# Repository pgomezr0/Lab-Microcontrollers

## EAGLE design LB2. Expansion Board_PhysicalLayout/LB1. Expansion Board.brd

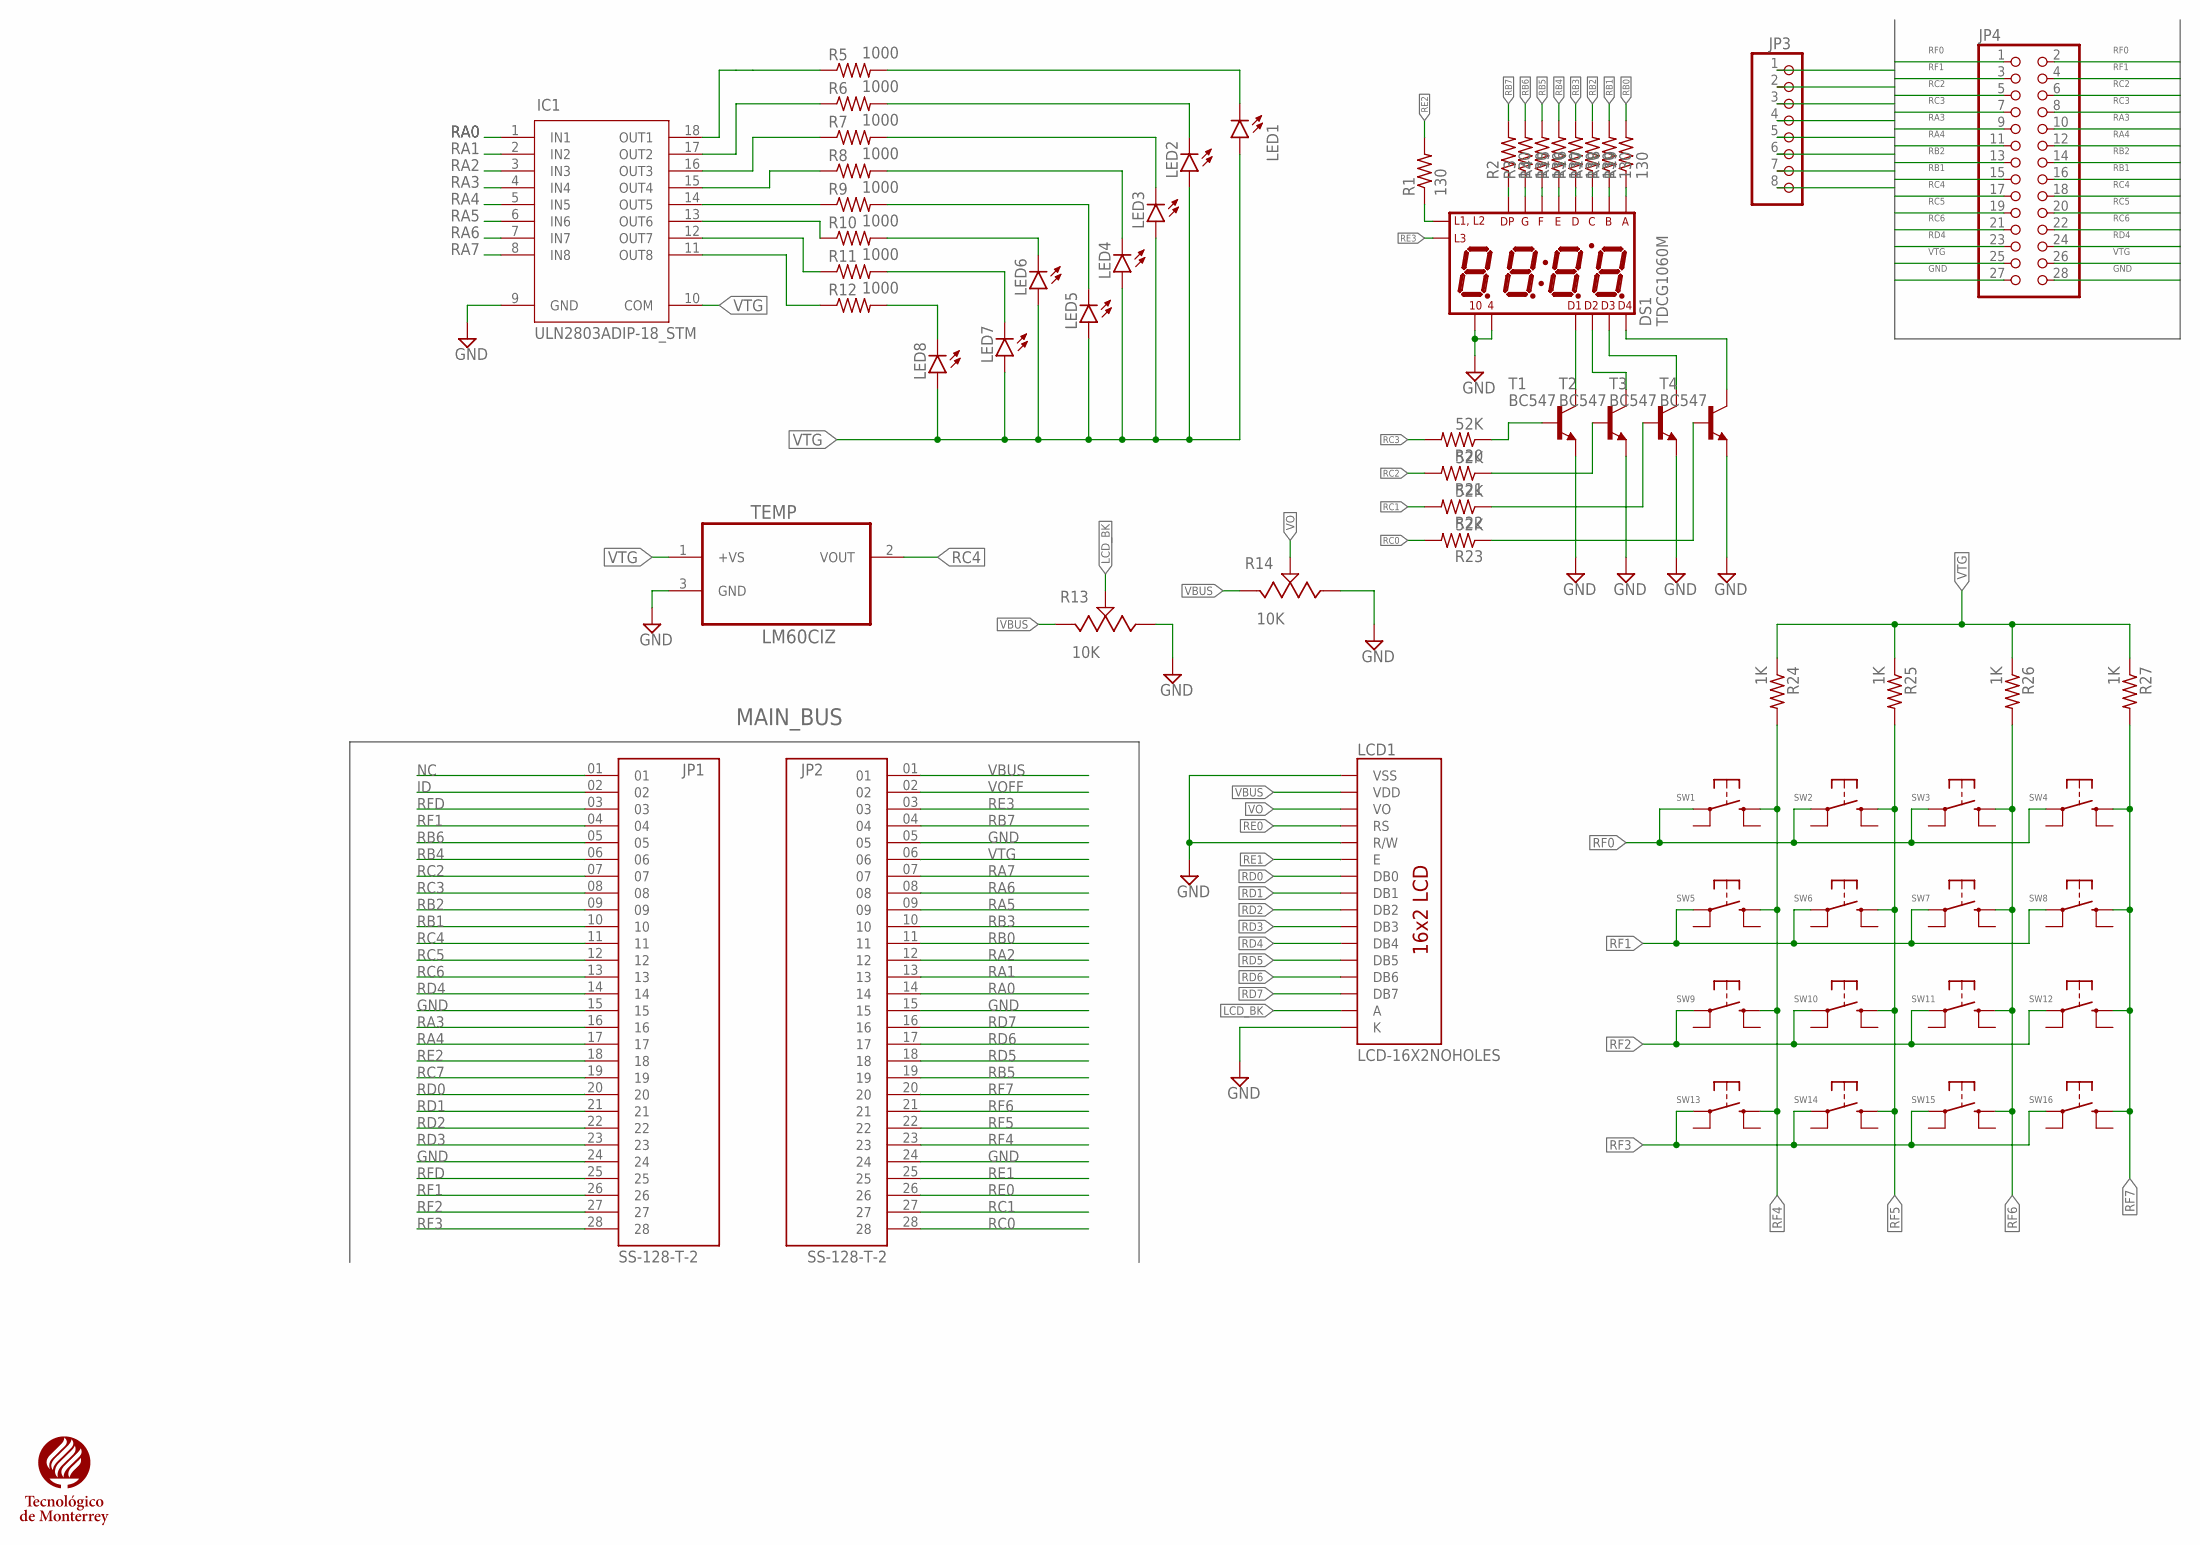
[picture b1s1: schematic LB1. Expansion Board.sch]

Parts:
DS1: TDCG1060M; DISPLAY_TDCG1060M
IC1: ULN2803ADIP-18_STM; DIP-18_STM
JP1, JP2: SS-128-T-2; SAMTEC_SS-128-T-2
JP3: PINHD-1X8BIG; 1X08-BIG
JP4: PINHD-2X14-CB; 2X14-BIG
LCD1: LCD-16X2NOHOLES; LCD-16X2_NOHOLESNOSILK
LED1, LED2, LED3, LED4, LED5, LED6, LED7, LED8: LED3MM
R1, R2, R3, R4, R15, R16, R17, R18, R19: 130; 0207/10
R5, R6, R7, R8, R9, R10, R11, R12: 1000; 0207/10
R13, R14: 10K; 3362P-1-103LF
R20, R21, R22, R23: 52K; 0207/10
R24, R25, R26, R27: 1K; 0207/10
SW1, SW2, SW3, SW4, SW5, SW6, SW7, SW8, SW9, SW10, SW11, SW12, SW13, SW14, SW15, SW16: 1825910-2; TE_1825910-2
T1, T2, T3, T4: BC547; TO92
TEC1: TEC_LOGO
TEMP: LM60CIZ; TO92/

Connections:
GND: DS1.4, DS1.10, IC1.9 (GND), JP1.15, JP1.24, JP2.05, JP2.15, JP2.24, JP3.1, JP4.27, JP4.28, LCD1.1 (VSS), LCD1.5 (R/W), LCD1.16 (K), R13.3, R14.3, T1.1 (E), T2.1 (E), T3.1 (E), T4.1 (E), TEMP.3 (GND)
ID: JP1.02
LCD_BK: LCD1.15 (A), R13.2
unnamed: LED1.K (C), R5.2
unnamed: IC1.18 (OUT1), R5.1
unnamed: IC1.17 (OUT2), R6.1
unnamed: LED2.K (C), R6.2
unnamed: IC1.16 (OUT3), R7.1
unnamed: IC1.15 (OUT4), R8.1
unnamed: IC1.14 (OUT5), R9.1
unnamed: IC1.13 (OUT6), R10.1
unnamed: IC1.12 (OUT7), R11.1
unnamed: IC1.11 (OUT8), R12.1
unnamed: LED3.K (C), R7.2
unnamed: LED4.K (C), R8.2
unnamed: LED5.K (C), R9.2
unnamed: LED6.K (C), R10.2
unnamed: LED8.K (C), R12.2
unnamed: LED7.K (C), R11.2
unnamed: R20.1, T1.2 (B)
unnamed: LED1.A, LED2.A, LED3.A, LED4.A, LED5.A, LED6.A, LED7.A, LED8.A
unnamed: DS1.12 (L1_L2), R1.1
unnamed: DS1.7 (DP), R2.1
unnamed: DS1.15 (G), R3.1
unnamed: DS1.11 (F), R4.1
unnamed: DS1.5 (E), R15.1
unnamed: DS1.3 (D), R16.1
unnamed: DS1.13 (C), R17.1
unnamed: DS1.16 (B), R18.1
unnamed: DS1.14 (A), R19.1
unnamed: R21.1, T2.2 (B)
unnamed: R22.1, T3.2 (B)
unnamed: R23.1, T4.2 (B)
unnamed: DS1.1 (DIG1), T1.3 (C)
unnamed: DS1.2 (DIG2), T2.3 (C)
unnamed: DS1.6 (DIG3), T3.3 (C)
unnamed: DS1.8 (DIG4), T4.3 (C)
NC: JP1.01
RA0: IC1.1 (IN1), JP2.14
RA1: IC1.2 (IN2), JP2.13
RA2: IC1.3 (IN3), JP2.12
RA3: IC1.4 (IN4), JP1.16, JP3.2, JP4.9, JP4.10
RA4: IC1.5 (IN5), JP1.17, JP3.3, JP4.11, JP4.12
RA5: IC1.6 (IN6), JP2.09
RA6: IC1.7 (IN7), JP2.08
RA7: IC1.8 (IN8), JP2.07
RB0: JP2.11, R19.2
RB1: JP1.10, JP3.4, JP4.15, JP4.16, R18.2
RB2: JP1.09, JP3.5, JP4.13, JP4.14, R17.2
RB3: JP2.10, R16.2
RB4: JP1.06, R15.2
RB5: JP2.19, R4.2
RB6: JP1.05, R3.2
RB7: JP2.04, R2.2
RC0: JP2.28, R23.2
RC1: JP2.27, R22.2
RC2: JP1.07, JP3.6, JP4.5, JP4.6, R21.2
RC3: JP1.08, JP3.7, JP4.7, JP4.8, R20.2
RC4: JP1.11, JP3.8, JP4.17, JP4.18, TEMP.2 (VOUT)
RC5: JP1.12, JP4.19, JP4.20
RC6: JP1.13, JP4.21, JP4.22
RC7: JP1.19
RD0: JP1.20, LCD1.7 (DB0)
RD1: JP1.21, LCD1.8 (DB1)
RD2: JP1.22, LCD1.9 (DB2)
RD3: JP1.23, LCD1.10 (DB3)
RD4: JP1.14, JP4.23, JP4.24, LCD1.11 (DB4)
RD5: JP2.18, LCD1.12 (DB5)
RD6: JP2.17, LCD1.13 (DB6)
RD7: JP2.16, LCD1.14 (DB7)
RE0: JP2.26, LCD1.4 (RS)
RE1: JP2.25, LCD1.6 (E)
RE2: JP1.18, R1.2
RE3: DS1.9 (L3), JP2.03
RF0: JP4.1, JP4.2, SW1.1, SW2.1, SW3.1, SW4.1
RF1: JP1.04, JP1.26, JP4.3, JP4.4, SW5.1, SW6.1, SW7.1, SW8.1
RF2: JP1.27, SW9.1, SW10.1, SW11.1, SW12.1
RF3: JP1.28, SW13.1, SW14.1, SW15.1, SW16.1
RF4: JP2.23, R24.2, SW1.2 (S), SW5.2 (S), SW9.2 (S), SW13.2 (S)
RF5: JP2.22, R25.2, SW2.2 (S), SW6.2 (S), SW10.2 (S), SW14.2 (S)
RF6: JP2.21, R26.2, SW3.2 (S), SW7.2 (S), SW11.2 (S), SW15.2 (S)
RF7: JP2.20, R27.2, SW4.2 (S), SW8.2 (S), SW12.2 (S), SW16.2 (S)
RFD: JP1.03, JP1.25
VBUS: JP2.01, LCD1.2 (VDD), R13.1, R14.1
VO: LCD1.3 (VO), R14.2
VOFF: JP2.02
VTG: IC1.10 (COM), JP2.06, JP4.25, JP4.26, R24.1, R25.1, R26.1, R27.1, TEMP.1 (+VS)

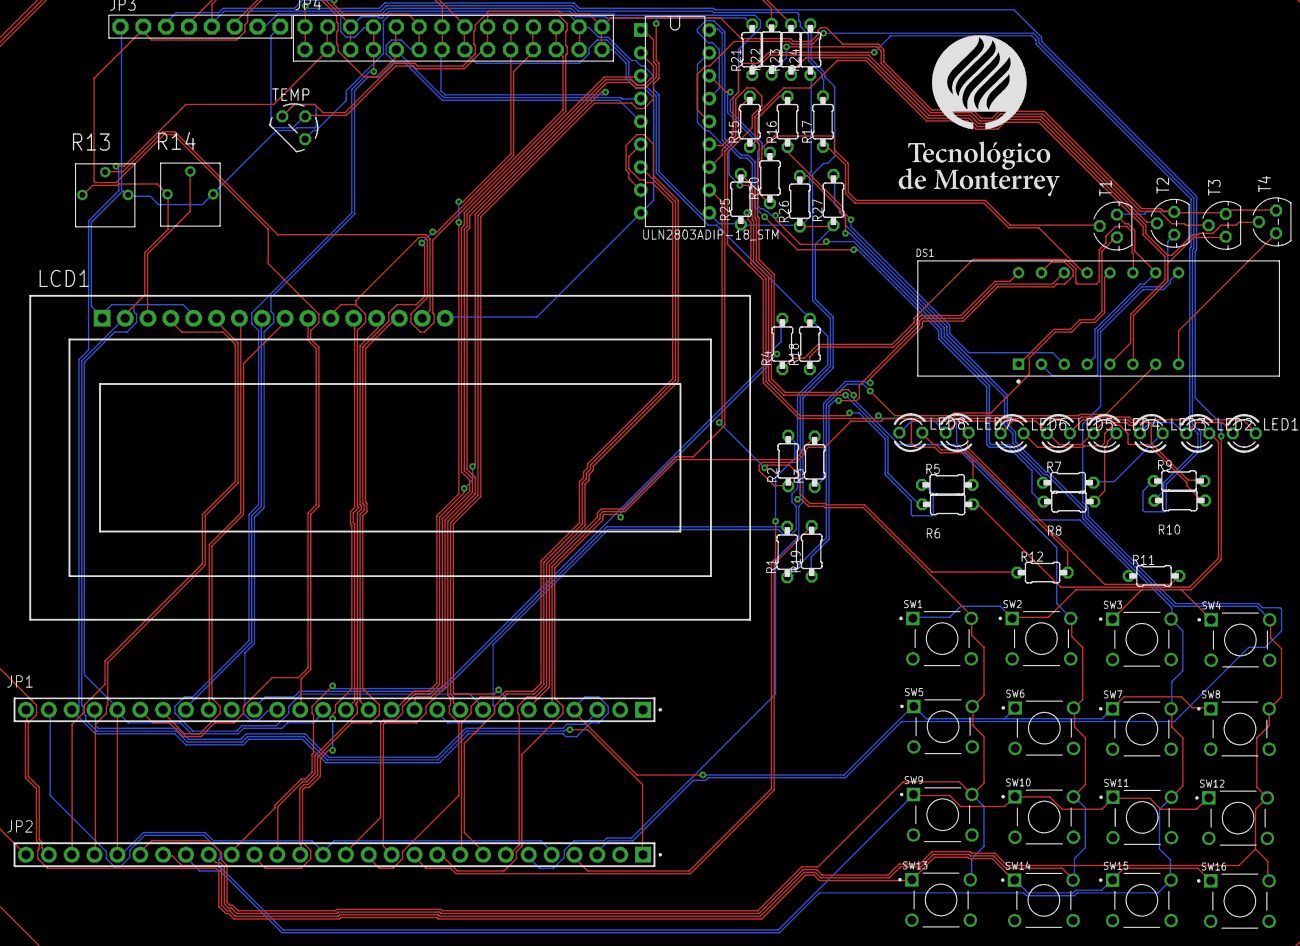
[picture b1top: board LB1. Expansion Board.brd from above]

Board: 2 copper layers, 64 parts (0 on the bottom side), 83 nets.

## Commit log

2022-08-16 Initial commit with lab 1
    Schematic diagram and Eagle project file without ERC errors
2022-08-30 Lab 2 physical layout
    Continuation of creation of PCB, including outing all of the electrical connections and zip file with Gerber files
2022-08-30 add Video_Link.txt
2022-09-06 lab 3 basics
2022-09-07 memory access exercises
2022-10-04 lab 5 c exercises
2022-12-03 Lab 6

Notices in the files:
parts and their libraries:
TE2015_Microcontroladores: COPYRIGHT: Copyright (C) 2022 Ultra Librarian. All rights reserved.
